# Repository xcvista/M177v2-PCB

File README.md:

# M177v2 Reduced User Interface for Raspberry Pi

EAGLE board files

## More information

M177v2 is licensed under [3-clause BSD license](LICENSE.md).

Copyright &copy; 2015 Max Chan. All rights reserved.

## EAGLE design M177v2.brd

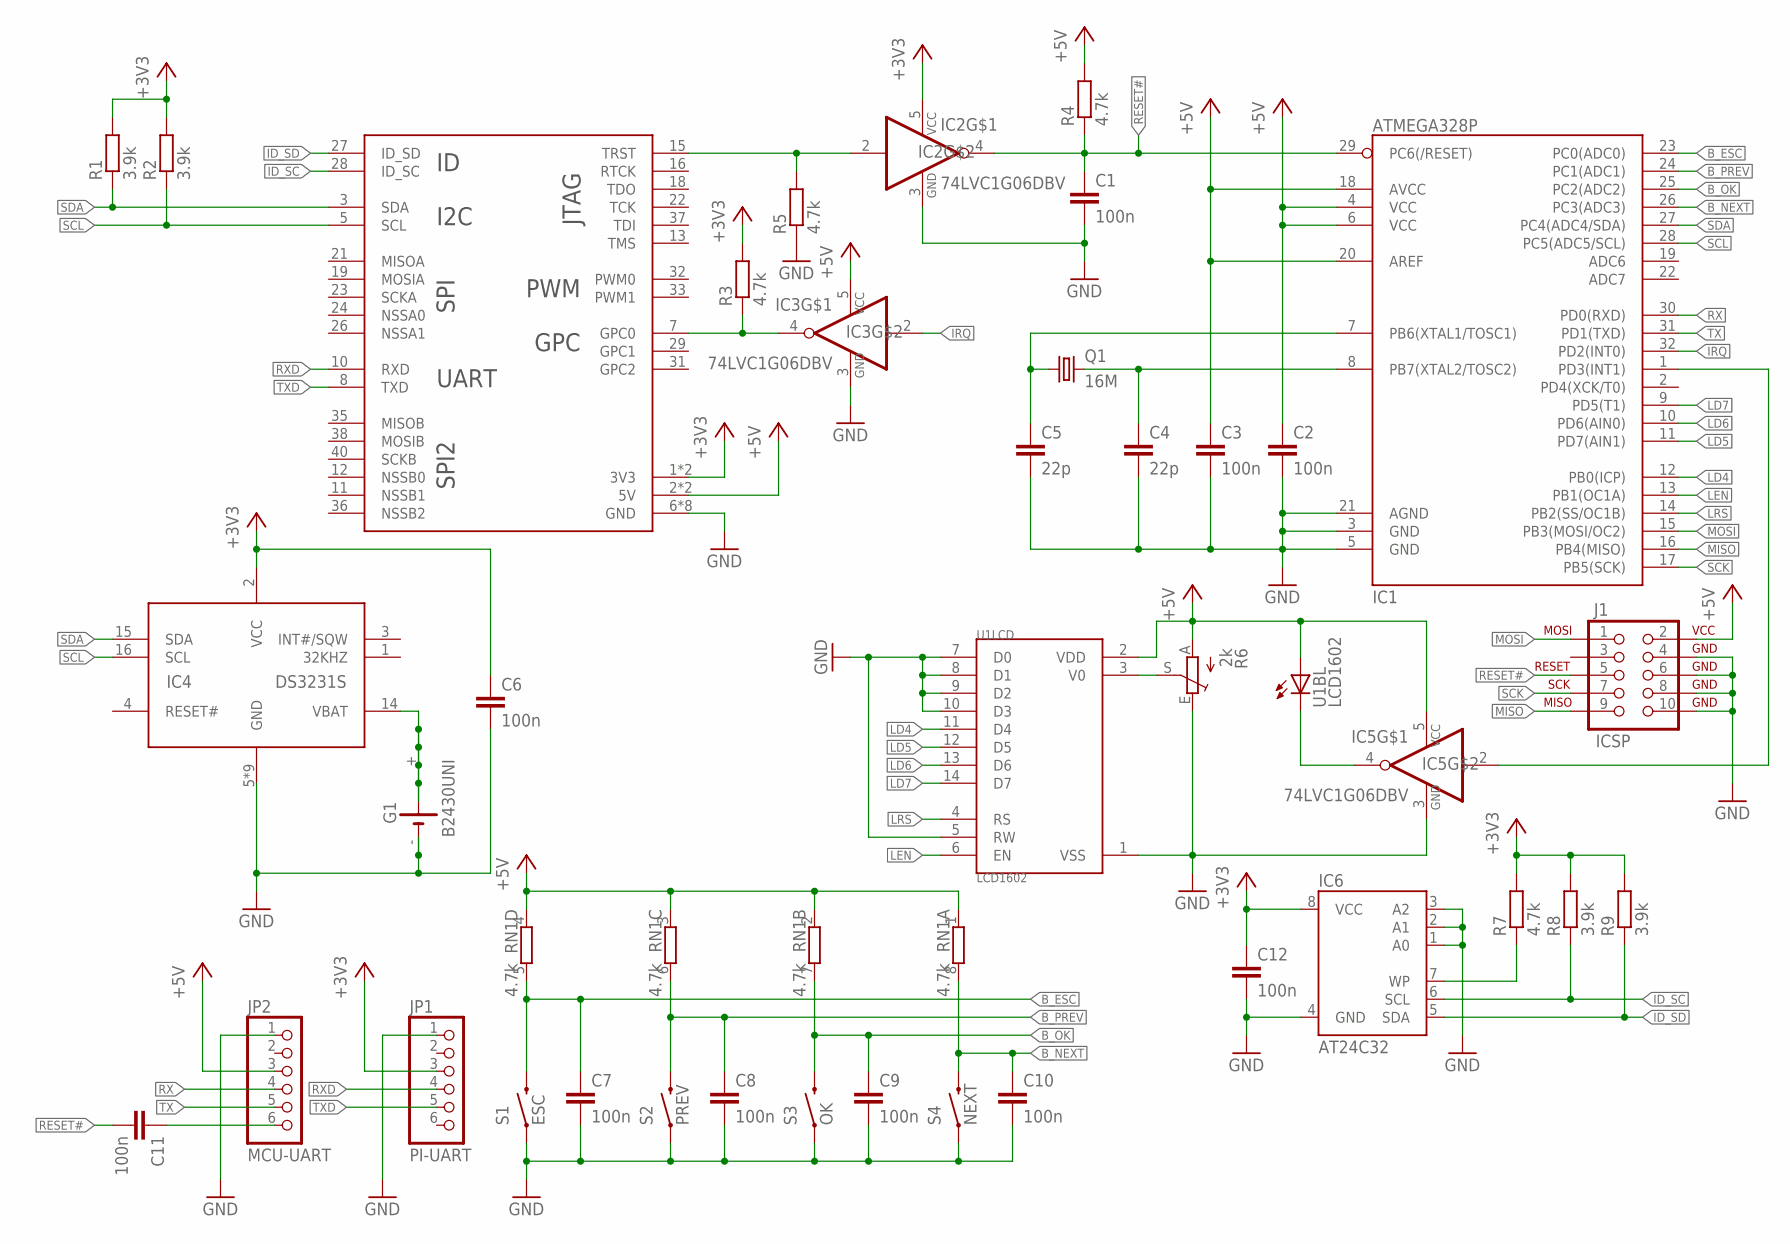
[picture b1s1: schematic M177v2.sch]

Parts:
C1, C2, C3, C6, C7, C8, C9, C10, C11, C12: 100n; C0603
C4, C5: 22p; C0603
G1: B2430UNI
IC1: ATMEGA328P; TQFP32-08
IC2, IC3, IC5: 74LVC1G06DBV; SOT23-5
IC4: DS3231S; SO16W
IC6: AT24C32; SO-08
J1: ICSP; 2X5-SHROUDED
JP1: PI-UART; 1X06
JP2: MCU-UART; 1X06
Q1: 16M; HC49/S
R1, R2, R8, R9: 3.9k; R0603
R3, R4, R5, R7: 4.7k; R0603
R6: 2k; CA6V
RN1: 4.7k; 0603-ARV
S1: ESC; TACTILE-SWITCH-1101NE
S2: PREV; TACTILE-SWITCH-1101NE
S3: OK; TACTILE-SWITCH-1101NE
S4: NEXT; TACTILE-SWITCH-1101NE
U1: LCD1602; LCD1602A
U2: RASPI-B+H; HAT

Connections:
+3V3: C6.1, C12.1, IC2.5 (VCC), IC4.2 (VCC), IC6.8 (VCC), JP1.3, R1.2, R2.2, R3.2, R7.2, R8.2, R9.2, U2.1 (3V3), U2.17 (3V3)
+5V: C2.1, C3.1, IC1.4 (VCC), IC1.6 (VCC), IC1.18 (AVCC), IC1.20 (AREF), IC3.5 (VCC), IC5.5 (VCC), J1.2 (VCC), JP2.3, R4.2, R6.A, RN1.1, RN1.2 (1), RN1.3 (1), RN1.4 (1), U1.2 (VDD), U1.15 (A), U2.2 (5V), U2.4 (5V)
B_ESC: C7.1, IC1.23 (PC0(ADC0)), RN1.5 (2), S1.2
B_NEXT: C10.1, IC1.26 (PC3(ADC3)), RN1.8 (2), S4.2
B_OK: C9.1, IC1.25 (PC2(ADC2)), RN1.7 (2), S3.2
B_PREV: C8.1, IC1.24 (PC1(ADC1)), RN1.6 (2), S2.2
GND: C1.2, C2.2, C3.2, C4.2, C5.2, C6.2, C7.2, C8.2, C9.2, C10.2, C12.2, G1.-, G1.-@1 (-), IC1.3 (GND), IC1.5 (GND), IC1.21 (AGND), IC2.3 (GND), IC3.3 (GND), IC4.5 (GND), IC4.6 (GND), IC4.7 (GND), IC4.8 (GND), IC4.9 (GND), IC4.10 (GND), IC4.11 (GND), IC4.12 (GND), IC4.13 (GND), IC5.3 (GND), IC6.1 (A0), IC6.2 (A1), IC6.3 (A2), IC6.4 (GND), J1.4 (GND), J1.6 (GND), J1.8 (GND), J1.10 (GND), JP1.1, JP2.1, R5.1, R6.E, S1.1, S2.1, S3.1, S4.1, U1.1 (VSS), U1.5 (RW), U1.7 (D0), U1.8 (D1), U1.9 (D2), U1.10 (D3), U2.6 (GND), U2.9 (GND), U2.14 (GND), U2.20 (GND), U2.25 (GND), U2.30 (GND), U2.34 (GND), U2.39 (GND)
ID_SC: IC6.6 (SCL), R8.1, U2.28 (ID_SC)
ID_SD: IC6.5 (SDA), R9.1, U2.27 (ID_SD)
IRQ: IC1.32 (PD2(INT0)), IC3.2 (I)
IRQ#: IC3.4 (O), R3.1, U2.7 (GPC0)
LD4: IC1.12 (PB0(ICP)), U1.11 (D4)
LD5: IC1.11 (PD7(AIN1)), U1.12 (D5)
LD6: IC1.10 (PD6(AIN0)), U1.13 (D6)
LD7: IC1.9 (PD5(T1)), U1.14 (D7)
LEN: IC1.13 (PB1(OC1A)), U1.6 (EN)
LRS: IC1.14 (PB2(SS/OC1B)), U1.4 (RS)
MISO: IC1.16 (PB4(MISO)), J1.9 (MISO)
MOSI: IC1.15 (PB3(MOSI/OC2)), J1.1 (MOSI)
unnamed: G1.+, G1.+@1 (+), G1.+@2 (+), G1.+@3 (+), G1.+@4 (+), IC4.14 (VBAT)
unnamed: C4.1, IC1.8 (PB7(XTAL2/TOSC2)), Q1.2
unnamed: IC2.2 (I), R5.2, U2.15 (TRST)
unnamed: R6.S, U1.3 (V0)
unnamed: C5.1, IC1.7 (PB6(XTAL1/TOSC1)), Q1.1
unnamed: IC5.4 (O), U1.16 (C)
unnamed: IC1.1 (PD3(INT1)), IC5.2 (I)
unnamed: C11.1, JP2.6
unnamed: IC6.7 (WP), R7.1
RESET#: C1.1, C11.2, IC1.29 (PC6(/RESET)), IC2.4 (O), J1.5 (RESET), R4.1
RX: IC1.30 (PD0(RXD)), JP2.4
RXD: JP1.4, U2.10 (RXD)
SCK: IC1.17 (PB5(SCK)), J1.7 (SCK)
SCL: IC1.28 (PC5(ADC5/SCL)), IC4.16 (SCL), R2.1, U2.5 (SCL)
SDA: IC1.27 (PC4(ADC4/SDA)), IC4.15 (SDA), R1.1, U2.3 (SDA)
TX: IC1.31 (PD1(TXD)), JP2.5
TXD: JP1.5, U2.8 (TXD)

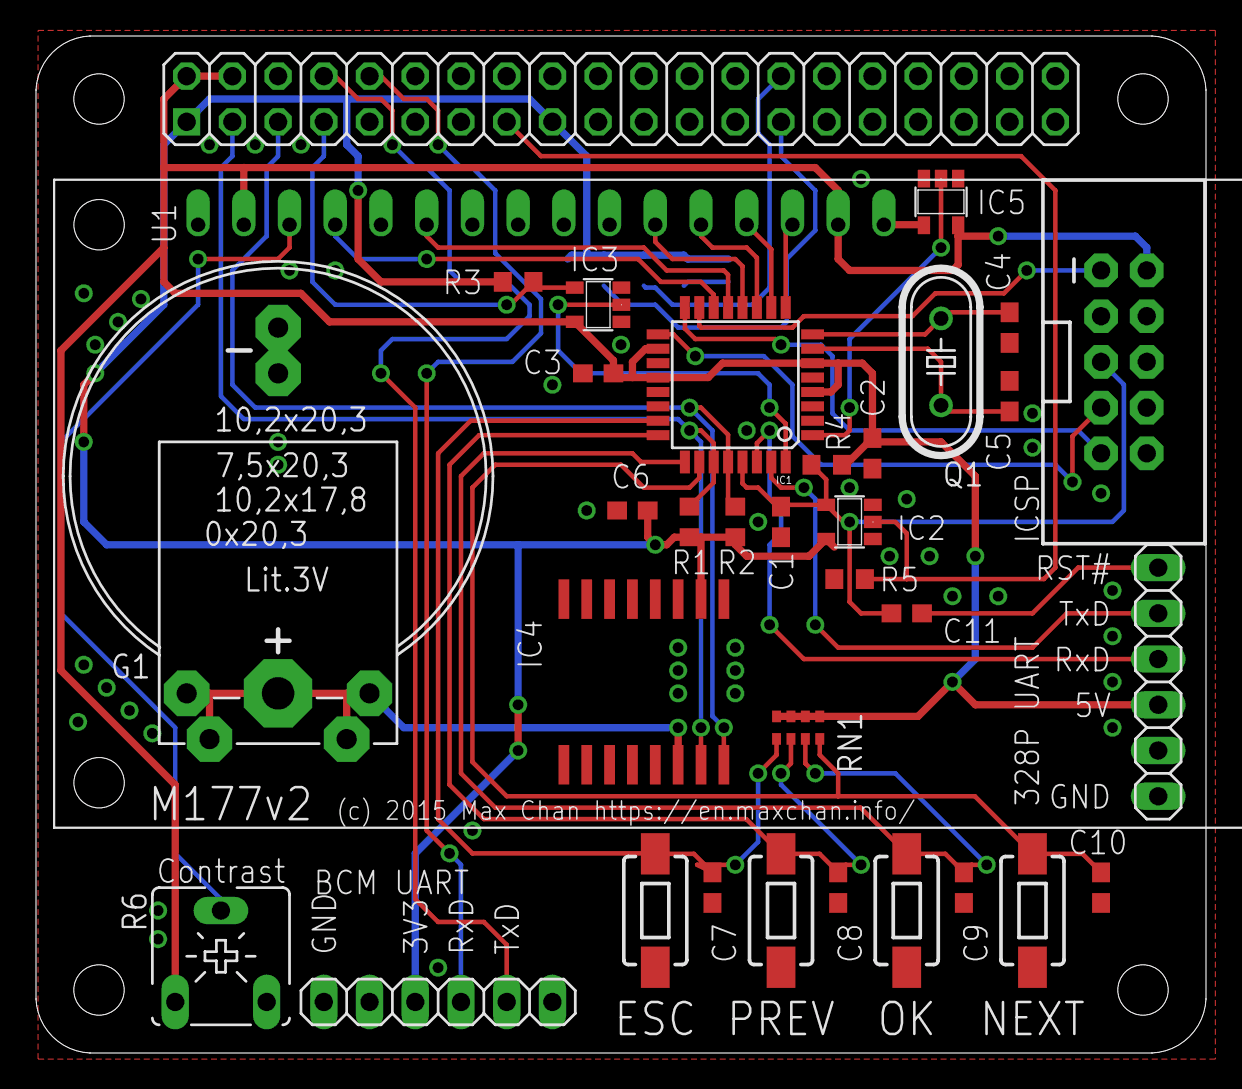
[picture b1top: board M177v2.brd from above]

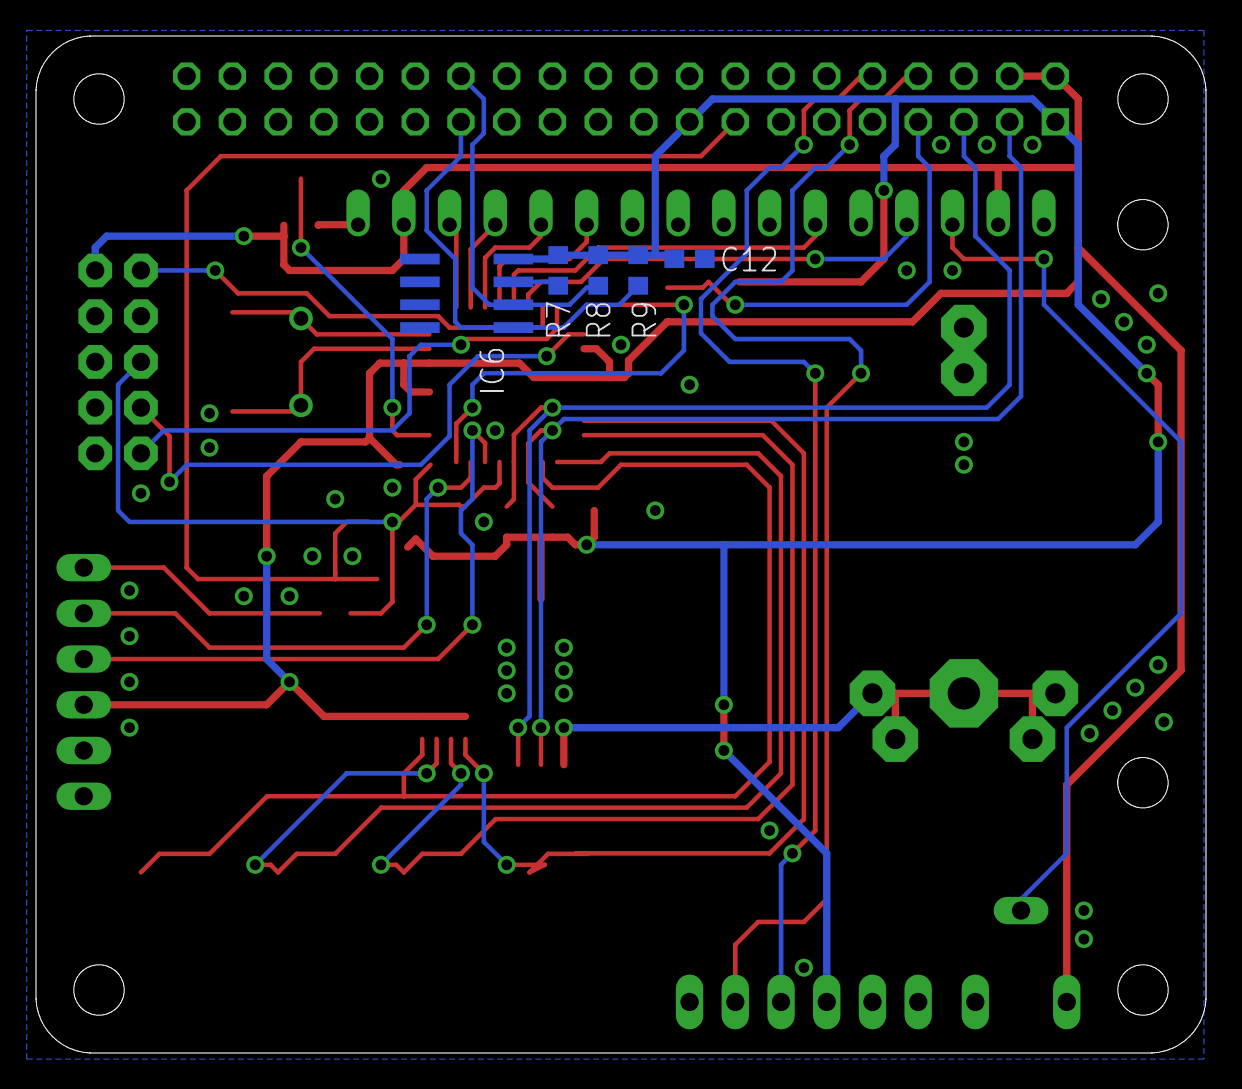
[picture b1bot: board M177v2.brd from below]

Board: 2 copper layers, 65.0 x 56.5 mm, 39 parts (5 on the bottom side), 36 nets.

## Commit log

2015-09-22 Finished: M177v2
2015-09-22 Added documentation
2015-09-22 Documentation

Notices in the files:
M177v2.brd:
(c) 2015 Max Chan https://en.maxchan.info
parts and their libraries:
SparkFun-DigitalIC: Licensing: Creative Commons ShareAlike 4.0 International - https://creativecommons.org/licenses/by-sa/4.0
